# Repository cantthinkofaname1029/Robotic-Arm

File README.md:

Robotic Arm
===========

2015 Robotic Arm Hardware/Software
- Please see the wiki for more information about the subjects below.

Hardware:
---------

###PCBs
-Version 3 of the arm board aka "the old-new arm board" is a remake of V2 (the old arm board currently on Phoenix). It is designed to have the exact same functionality as Phoenix, without using a master-slave protocol. It features a TI Launchpad Stellaris as the central CPU, 3 motor controllers that can connect to up to two motors each, and an RS-485 connection to the old dynamixel (MX-64R). It has the additional capability of communicating with the end effector via XBee and receives power from PORN.

-Version 4 of the arm board aka "the illuminati board" is the latest version. It features a TIVA-C for it's central processor and extends the functionality of Version 3. It only has one motor controller for the Pololu actuator, but it connects to multiple Dynamixels over TTL. There is a 9DOF IMU added on the board for additional control capabilities. it also receives power from PORN.

###Motors
-The base of the arm as well as the elbow joints use the Dynamixel MX-64T. It operates at a MAXIMUM voltage of 14.8V. Information on these motors can be found here:

http://support.robotis.com/en/product/dynamixel/mx_series/mx-64.htm

http://support.robotis.com/en/techsupport_eng.htm#product/dynamixel/mx_series/mx-64.htm

http://support.robotis.com/en/techsupport_eng.htm#software/dynamixelsdk.htm

-The wrist joints on the arm use the Dynamixel MX-28T. It operates at a MAXIMUM voltage of 14.8V. Information on these motors can be found here:

http://support.robotis.com/en/product/dynamixel/mx_series/mx-28.htm

http://support.robotis.com/en/techsupport_eng.htm#product/dynamixel/mx_series/mx-28.htm

http://support.robotis.com/en/techsupport_eng.htm#software/dynamixelsdk.htm

-The shoulder joint of the arm uses a Pololu Linear Actuator with an 8" stroke and a potentiometer for feedback. It operates at a MAXIMUM of 12V. It will be controlled using an on-board motor controller. Information on this actuator can be found here:

https://www.pololu.com/product/2337/specs

Software:
---------

-Software for V3 is nearing completion. It will have basic functionality for the arm for open-loop controls.

-Software for V4 has not started yet. It will be a port from the V3 code to TivaWare.

-After the V4 code has been completed for basic functionality, we need to start writing the framework for more exotic control methods.

-There is a Dynamixel SDK found here:

http://support.robotis.com/en/software/dynamixelsdk.htm

-There is a fully-written Dynamixel Library written for Arduino here:

http://savageelectronics.blogspot.com/2011/01/arduino-y-dynamixel-ax-12.html

if you can't read spanish or use google translate, the various libraries are found here:

http://savageelectronics.blogspot.com/2011/08/actualizacion-biblioteca-dynamixel.html

These will probably be useful to us when writing the further code.

-We may have to write our own PID control for the actuator in the future. Get an introduction to PID for arduino here:

http://brettbeauregard.com/blog/2011/04/improving-the-beginners-pid-introduction/

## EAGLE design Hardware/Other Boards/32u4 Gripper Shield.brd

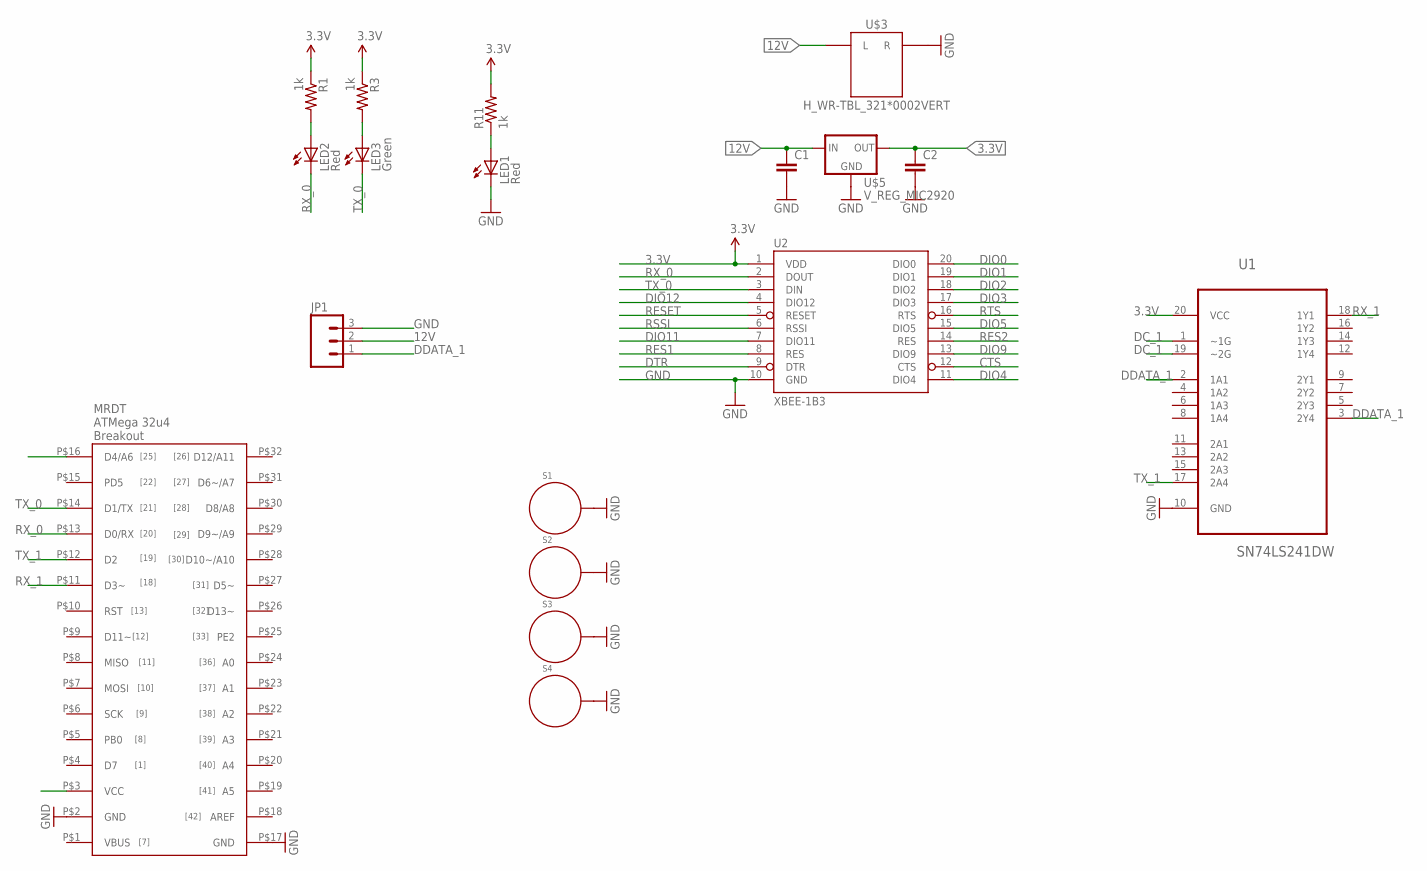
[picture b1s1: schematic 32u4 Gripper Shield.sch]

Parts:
C1, C2: CAP1206; 1206
JP1: M03PTH; 1X03
LED1, LED2: Red; LED-0603
LED3: Green; LED-0603
R1, R3, R11: 1k; 1206
S1, S2, S3, S4: STANDOFF_ELECTRICAL; STANDOFF-ELECTRICAL
U1: SN74LS241DW; SOIC127P1030X265-20N
U2: XBEE-1B3; XBEE-SMD
U$1: 32U4_BREAKOU_SMD; 32U3_MCU_DIP_SMD
U$3: H_WR-TBL_321*0002VERT; 691321100002
U$5: V_REG_MIC2920; SOT223

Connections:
3.3V: C2.1, R1.1, R3.1, R11.2, U1.20 (VCC), U2.1 (VDD), U$1.P$3 (VCC), U$5.3 (OUT)
12V: C1.1, JP1.2, U$3.L, U$5.1 (IN)
CTS: U2.12 (CTS)
DC_1: U1.1 (~1G), U1.19 (~2G), U$1.P$16 (D4/A6)
DDATA_1: JP1.1, U1.2 (1A1), U1.3 (2Y4)
DIO0: U2.20 (DIO0)
DIO1: U2.19 (DIO1)
DIO2: U2.18 (DIO2)
DIO3: U2.17 (DIO3)
DIO4: U2.11 (DIO4)
DIO5: U2.15 (DIO5)
DIO9: U2.13 (DIO9)
DIO11: U2.7 (DIO11)
DIO12: U2.4 (DIO12)
DTR: U2.9 (DTR)
GND: C1.2, C2.2, JP1.3, LED1.C, S1.P1, S2.P1, S3.P1, S4.P1, U1.10 (GND), U2.10 (GND), U$1.P$2 (GND), U$1.P$17 (GND), U$3.R, U$5.2 (GND), U$5.4 (GND)
unnamed: LED2.A, R1.2
unnamed: LED3.A, R3.2
unnamed: LED1.A, R11.1
RES1: U2.8 (RES)
RES2: U2.14 (RES)
RESET: U2.5 (RESET)
RSSI: U2.6 (RSSI)
RTS: U2.16 (RTS)
RX_0: LED2.C, U2.2 (DOUT), U$1.P$13 (D0/RX)
RX_1: U1.18 (1Y1), U$1.P$11 (D3~)
TX_0: LED3.C, U2.3 (DIN), U$1.P$14 (D1/TX)
TX_1: U1.17 (2A4), U$1.P$12 (D2)

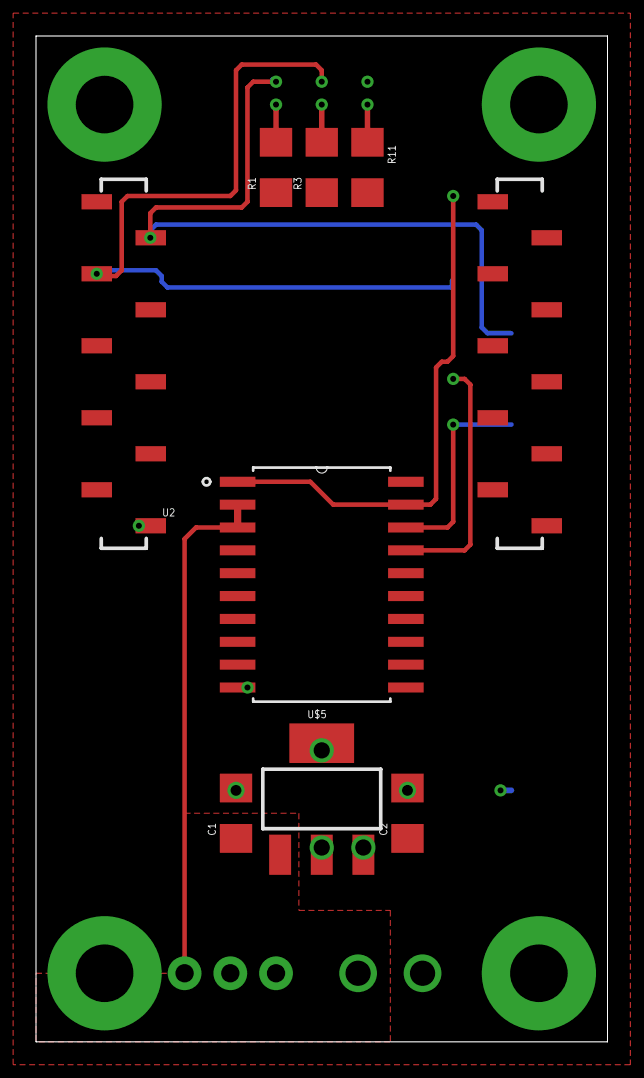
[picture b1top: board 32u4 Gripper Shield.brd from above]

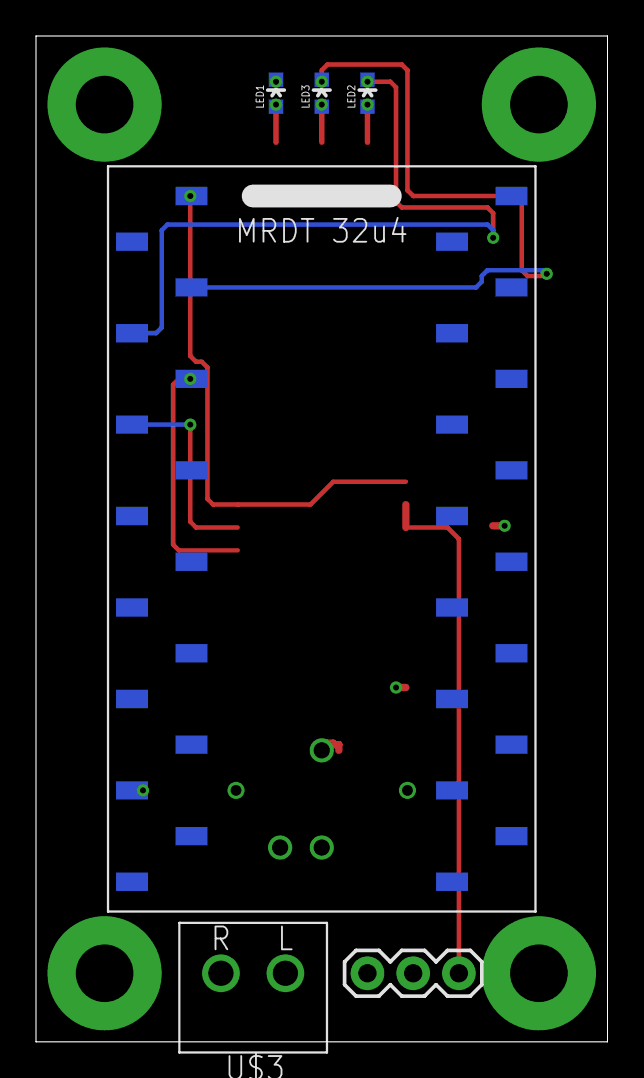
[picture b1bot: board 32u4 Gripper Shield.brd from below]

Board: 2 copper layers, 31.8 x 55.9 mm, 18 parts (6 on the bottom side), 12 nets.

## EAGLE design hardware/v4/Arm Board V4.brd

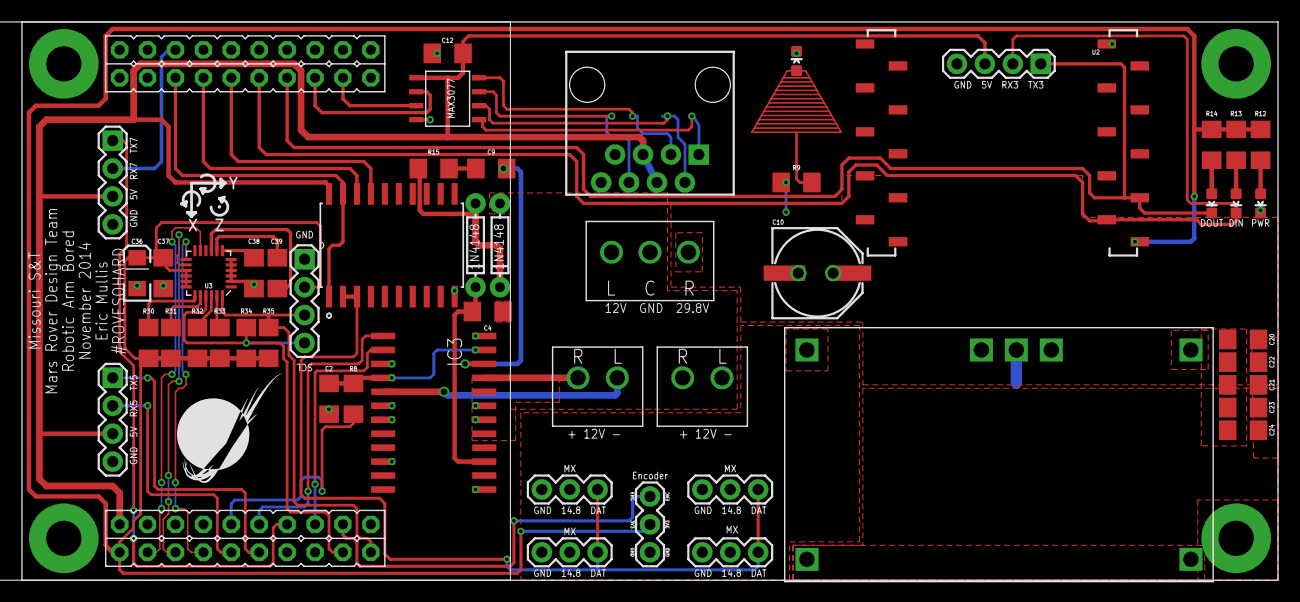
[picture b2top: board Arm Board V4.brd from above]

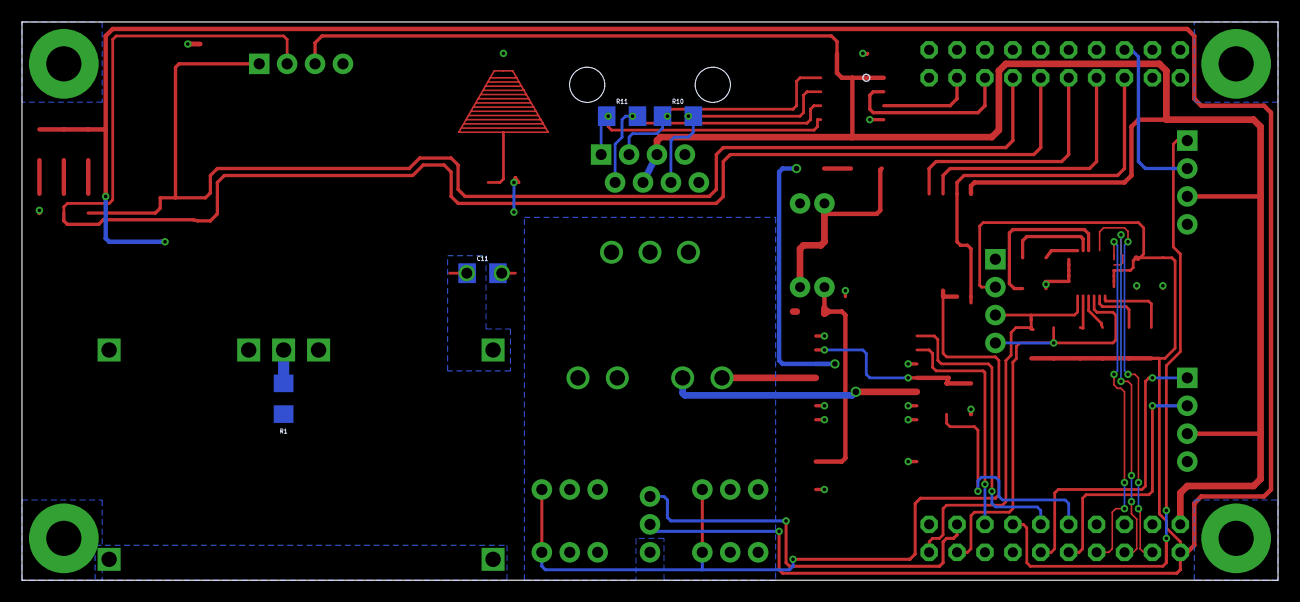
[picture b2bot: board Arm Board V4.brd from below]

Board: 2 copper layers, 114.3 x 50.8 mm, 60 parts (4 on the bottom side), 50 nets.

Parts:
C2: 5.6nF; 1206
C4: 220nF; 1206
C9: 10nF; 1206
C10: 330uF; PANASONIC_E
C11, C20: 1.0uF; 1206
C12: .1uF; 1206
C21, C22, C23, C24, C38: 4.7uF; 1206
C36: 10uF; EIA3216
C37: 1uF; 1206
C39: .22uF; 1206
D1, D2: 1N4148; DIODE-1N4148
IC3: L6206D; SO24
JP1, JP2, JP3, JP4: 1X04
JP7, JP9, JP10, JP11, JP12: 1X03
LED1, LED2, LED5: RED; LED-0603
LED3: GREEN; LED-0603
P1: STELLARIS-LAUNCHPADSTELLARIS-LAUNCHPAD-XL; LAUNCHPAD-XL
R1: 17.2k; 1206
R8: 100k; 1206
R9: 1.5k; 1206
R10, R11: 120 Ohm; 1206
R12, R13, R14: 1k; 1206
R15: 100; 1206
R30, R31, R32, R33, R34, R35: 10k; 1206
S1, S2, S3, S4: STANDOFF_ELECTRICAL; STANDOFF-ELECTRICAL
U1: SN74LS241DW; SOIC127P1030X265-20N
U2: XBEE-1B3; XBEE-SMD
U3: LSM9DS0; LGA-24
U$2: Q_PTN78020; R_PDSS-T7
U$3: RJ45-8PTH; RJ45-8
U$4: MAX3077; MAX3070E
U$5: 691321100003; 691322110003
U$6, U$7: H_WR-TBL_321*0002VERT; 691321100002

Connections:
14.8V: C10.+, C11.1, JP9.2, JP10.2, JP11.2, JP12.2, U$2.6
+3V3: C36.A, C37.1, JP4.2, JP7.2, P1.3.3V, R12.2, R13.1, R14.1, R30.2, R31.2, R32.2, R33.2, R34.2, R35.2, U2.1, U3.15, U3.16, U3.17, U3.18
+5V: C12.1, JP1.3, JP2.3, JP3.3, P1.VBUS, U1.20, U$3.4, U$3.5, U$4.VCC
+12V: C4.1, D2.A, IC3.17, IC3.20, U$5.L, U$7.L
A1: IC3.5, U$6.L
A2: IC3.21, U$6.R
CS_G: R30.1, U3.19
CS_XM: R31.1, U3.20
DC_1: P1.PB3, U1.1, U1.19
DDATA_1: JP9.3, JP10.3, JP11.3, JP12.3, U1.2, U1.3
EN_A: P1.PD2, R8.2
GND: C2.1, C10.-, C11.2, C12.2, C20.2, C21.2, C22.2, C23.2, C24.2, C36.C, C37.2, C38.2, IC3.3, IC3.6, IC3.7, IC3.10, IC3.13, IC3.18, IC3.19, IC3.24, JP1.4, JP2.4, JP3.4, JP4.1, JP7.1, JP9.1, JP10.1, JP11.1, JP12.1, LED1.C, LED5.C, P1.GND1, P1.GND2, R1.1, S1.P1, S2.P1, S3.P1, S4.P1, U1.10, U2.10, U3.2, U3.3, U3.4, U3.5, U3.6, U$2.1, U$2.7, U$3.7, U$3.8, U$4.GND, U$5.C, U$7.R
IN1_A: IC3.1, P1.PD3
IN2_A: IC3.2, P1.PE2
INT1_XM: P1.PB1, U3.13
INT2_XM: P1.PB0, U3.14
INT_G: P1.PB5, U3.11
LA_ENC: JP7.3, P1.PE3
unnamed: R11.1, U$3.2, U$4.Z
unnamed: R10.2, U$3.6, U$4.B
unnamed: R10.1, U$3.3, U$4.A
unnamed: LED2.A, R13.2
unnamed: R11.2, U$3.1, U$4.Y
unnamed: LED3.A, R14.2
unnamed: R1.2, U$2.4
unnamed: C39.1, U3.9
unnamed: C39.2, U3.8
unnamed: C38.1, U3.7
unnamed: LED5.A, R9.1
unnamed: D1.A, D2.C, R15.2
unnamed: C9.2, R15.1
unnamed: C9.1, IC3.22
unnamed: LED1.A, R12.1
OCD_A: C2.2, IC3.4, IC3.23, R8.1
RX_1: P1.PC4, U1.18
RX_2: P1.PD6, U$4.RO
RX_3: JP1.2, LED2.C, P1.PC6, U2.2
RX_5: JP3.2, P1.PE4
RX_7: JP2.2, P1.PE0
SCL: JP4.4, P1.PA6, R34.1, U3.21
SDA: JP4.3, P1.PA7, R35.1, U3.24
SDO_G: R32.1, U3.22
SDO_XM: R33.1, U3.23
TX_1: P1.PC5, U1.17
TX_2: P1.PD7, U$4.DI
TX_3: JP1.1, LED3.C, P1.PC7, U2.3
TX_5: JP3.1, P1.PE5
TX_7: JP2.1, P1.PE1
VBOOT: C4.2, D1.C, IC3.15
VIN: C20.1, C21.1, C22.1, C23.1, C24.1, R9.2, U$2.2, U$5.R

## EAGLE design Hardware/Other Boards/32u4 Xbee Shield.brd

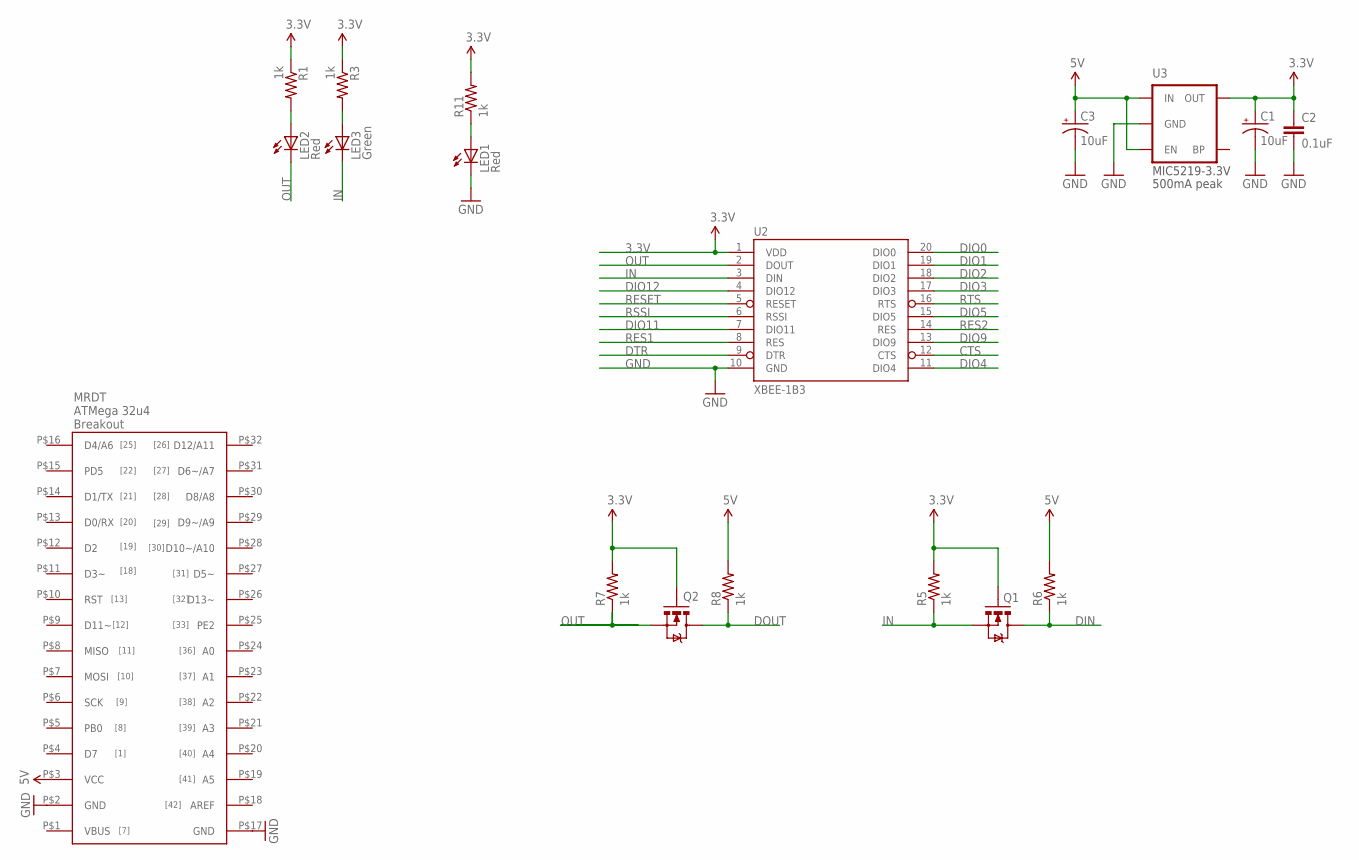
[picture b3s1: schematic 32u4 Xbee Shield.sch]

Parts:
C1, C3: 10uF; EIA3216
C2: 0.1uF; 1206
LED1, LED2: Red; LED-0603
LED3: Green; LED-0603
Q1, Q2: MOSFET-NCHANNELSMD; SOT23-3
R1, R3, R5, R6, R7, R8, R11: 1k; 1206
U2: XBEE-1B3; XBEE-SMD
U3: V_REG_LDOSMD; SOT23-5
U$1: 32U4_BREAKOU_SMD; 32U3_MCU_DIP_SMD

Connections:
3.3V: C1.A (+), C2.1, Q1.1 (G), Q2.1 (G), R1.1, R3.1, R5.2, R7.2, R11.2, U2.1 (VDD), U3.5 (OUT)
5V: C3.A (+), R6.2, R8.2, U3.1 (IN), U3.3 (EN), U$1.P$3 (VCC)
CTS: U2.12 (CTS)
DIN: Q1.3 (D), R6.1
DIO0: U2.20 (DIO0)
DIO1: U2.19 (DIO1)
DIO2: U2.18 (DIO2)
DIO3: U2.17 (DIO3)
DIO4: U2.11 (DIO4)
DIO5: U2.15 (DIO5)
DIO9: U2.13 (DIO9)
DIO11: U2.7 (DIO11)
DIO12: U2.4 (DIO12)
DOUT: Q2.3 (D), R8.1
DTR: U2.9 (DTR)
GND: C1.C (-), C2.2, C3.C (-), LED1.C, U2.10 (GND), U3.2 (GND), U$1.P$2 (GND), U$1.P$17 (GND)
IN: LED3.C, Q1.2 (S), R5.1, U2.3 (DIN)
unnamed: LED2.A, R1.2
unnamed: LED3.A, R3.2
unnamed: LED1.A, R11.1
OUT: LED2.C, Q2.2 (S), R7.1, U2.2 (DOUT)
RES1: U2.8 (RES)
RES2: U2.14 (RES)
RESET: U2.5 (RESET)
RSSI: U2.6 (RSSI)
RTS: U2.16 (RTS)

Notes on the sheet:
MIC5219-3.3V
500mA peak

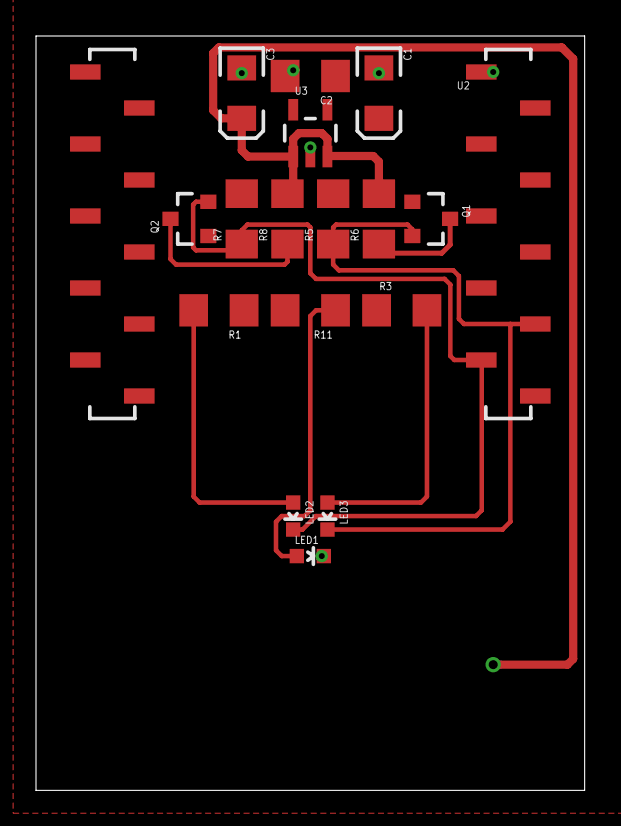
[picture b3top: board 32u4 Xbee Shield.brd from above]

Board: 2 copper layers, 30.5 x 41.9 mm, 18 parts (1 on the bottom side), 10 nets.

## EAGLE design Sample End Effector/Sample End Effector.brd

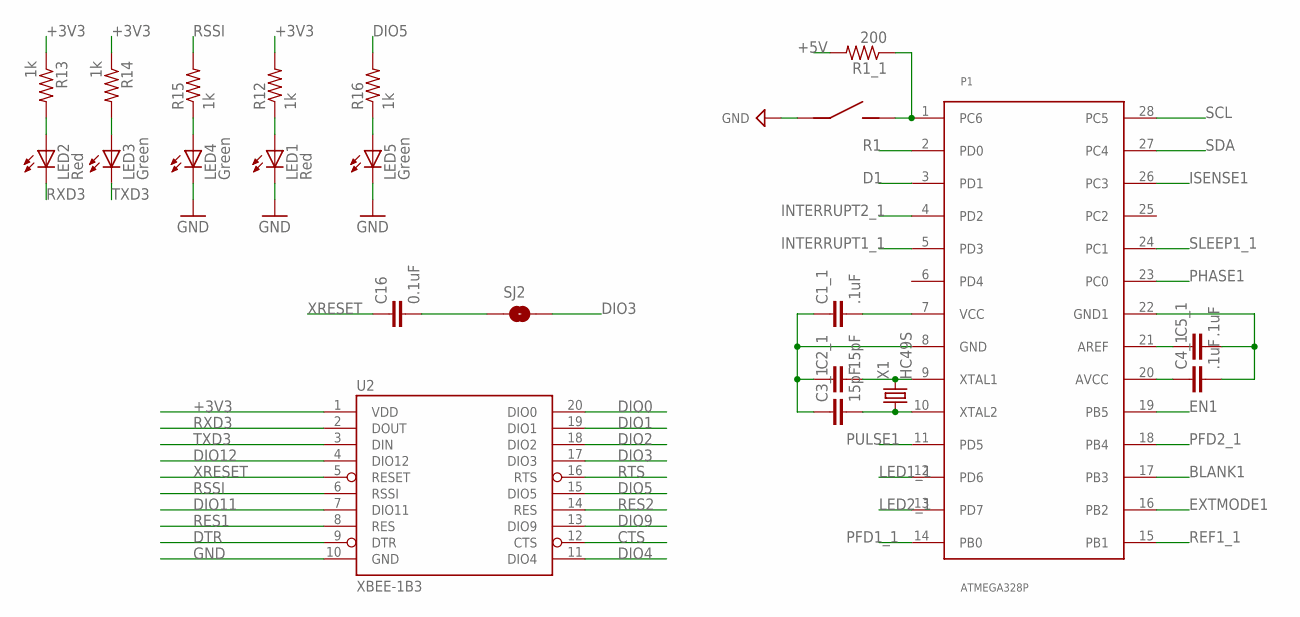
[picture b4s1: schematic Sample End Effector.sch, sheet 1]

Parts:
C1_1, C4_1, C5_1: .1uF; C_0805
C2_1, C3_1: 15pF; C_0805
C16: 0.1uF; 0603-CAP
LED1, LED2: Red; LED-0603
LED3, LED4, LED5: Green; LED-0603
P1: ATMEGA328P; DIP28
R1_1: 200; R_0805
R12, R13, R14, R15, R16: 1k; 0603-RES
S1: J_MC32857; J_TOGGLE
SJ2: SOLDERJUMPERTRACE; SJ_2S-TRACE
U2: XBEE-1B3; XBEE-SMD
X1: HC49S; HC-49

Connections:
+3V3: R12.2, R13.1, R14.1, U2.1 (VDD); also elsewhere on the board
+5V: C1_1.2, C4_1.1, P1.7 (VCC), P1.20 (AVCC), R1_1.2; also elsewhere on the board
BLANK1: P1.17 (PB3)
CTS: U2.12 (CTS)
D1: P1.3 (PD1)
DIO0: U2.20 (DIO0)
DIO1: U2.19 (DIO1)
DIO2: U2.18 (DIO2)
DIO3: SJ2.2, U2.17 (DIO3)
DIO4: U2.11 (DIO4)
DIO5: R16.2, U2.15 (DIO5)
DIO9: U2.13 (DIO9)
DIO11: U2.7 (DIO11)
DIO12: U2.4 (DIO12)
DTR: U2.9 (DTR)
EN1: P1.19 (PB5)
EXTMODE1: P1.16 (PB2)
GND: C1_1.1, C2_1.1, C3_1.1, C4_1.2, C5_1.2, LED1.C, LED4.C, LED5.C, P1.8 (GND), P1.22 (GND1), S1.P$1 (1), U2.10 (GND); also elsewhere on the board
INTERRUPT1_1: P1.5 (PD3)
INTERRUPT2_1: P1.4 (PD2)
ISENSE1: P1.26 (PC3)
LED1_1: P1.12 (PD6)
LED2_1: P1.13 (PD7)
unnamed: C3_1.2, P1.10 (XTAL2), X1.P$1 (1)
unnamed: LED2.A, R13.2
unnamed: LED3.A, R14.2
unnamed: LED4.A, R15.1
unnamed: C16.2, SJ2.1
unnamed: C2_1.2, P1.9 (XTAL1), X1.P$2 (2)
unnamed: C5_1.1, P1.21 (AREF)
unnamed: P1.1 (PC6), R1_1.1, S1.P$2 (2)
unnamed: LED1.A, R12.1
unnamed: LED5.A, R16.1
PFD1_1: P1.14 (PB0)
PFD2_1: P1.18 (PB4)
PHASE1: P1.23 (PC0)
PULSE1: P1.11 (PD5)
R1: P1.2 (PD0)
REF1_1: P1.15 (PB1)
RES1: U2.8 (RES)
RES2: U2.14 (RES)
RSSI: R15.2, U2.6 (RSSI)
RTS: U2.16 (RTS)
RXD3: LED2.C, U2.2 (DOUT)
SCL: P1.28 (PC5)
SDA: P1.27 (PC4)
SLEEP1_1: P1.24 (PC1)
TXD3: LED3.C, U2.3 (DIN)
XRESET: C16.1, U2.5 (RESET)

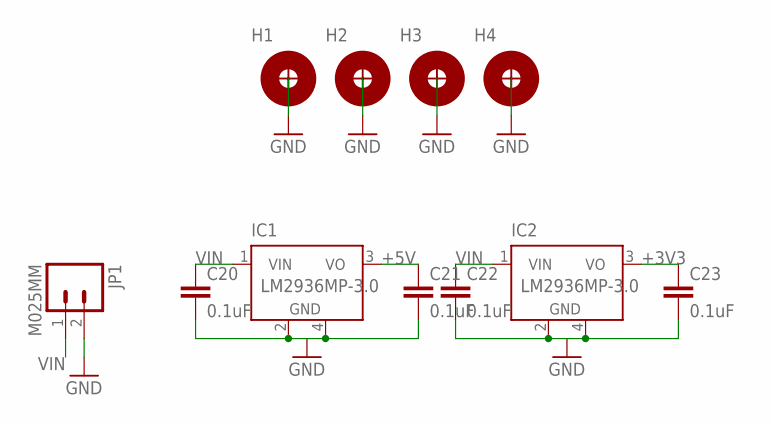
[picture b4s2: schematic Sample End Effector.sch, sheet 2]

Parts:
C20, C21, C22, C23: 0.1uF; 0603-CAP
H1, H2, H3, H4: H_MNTHOLE_#4
IC1, IC2: LM2936MP-3.0; SOT223
JP1: M025MM; SCREWTERMINAL-5MM-2

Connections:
+3V3: C23.1, IC2.3 (VO); also elsewhere on the board
+5V: C21.1, IC1.3 (VO); also elsewhere on the board
GND: C20.2, C21.2, C22.2, C23.2, H1.1, H2.1, H3.1, H4.1, IC1.2 (GND), IC1.4 (GND), IC2.2 (GND), IC2.4 (GND), JP1.2; also elsewhere on the board
VIN: C20.1, C22.1, IC1.1 (VIN), IC2.1 (VIN), JP1.1

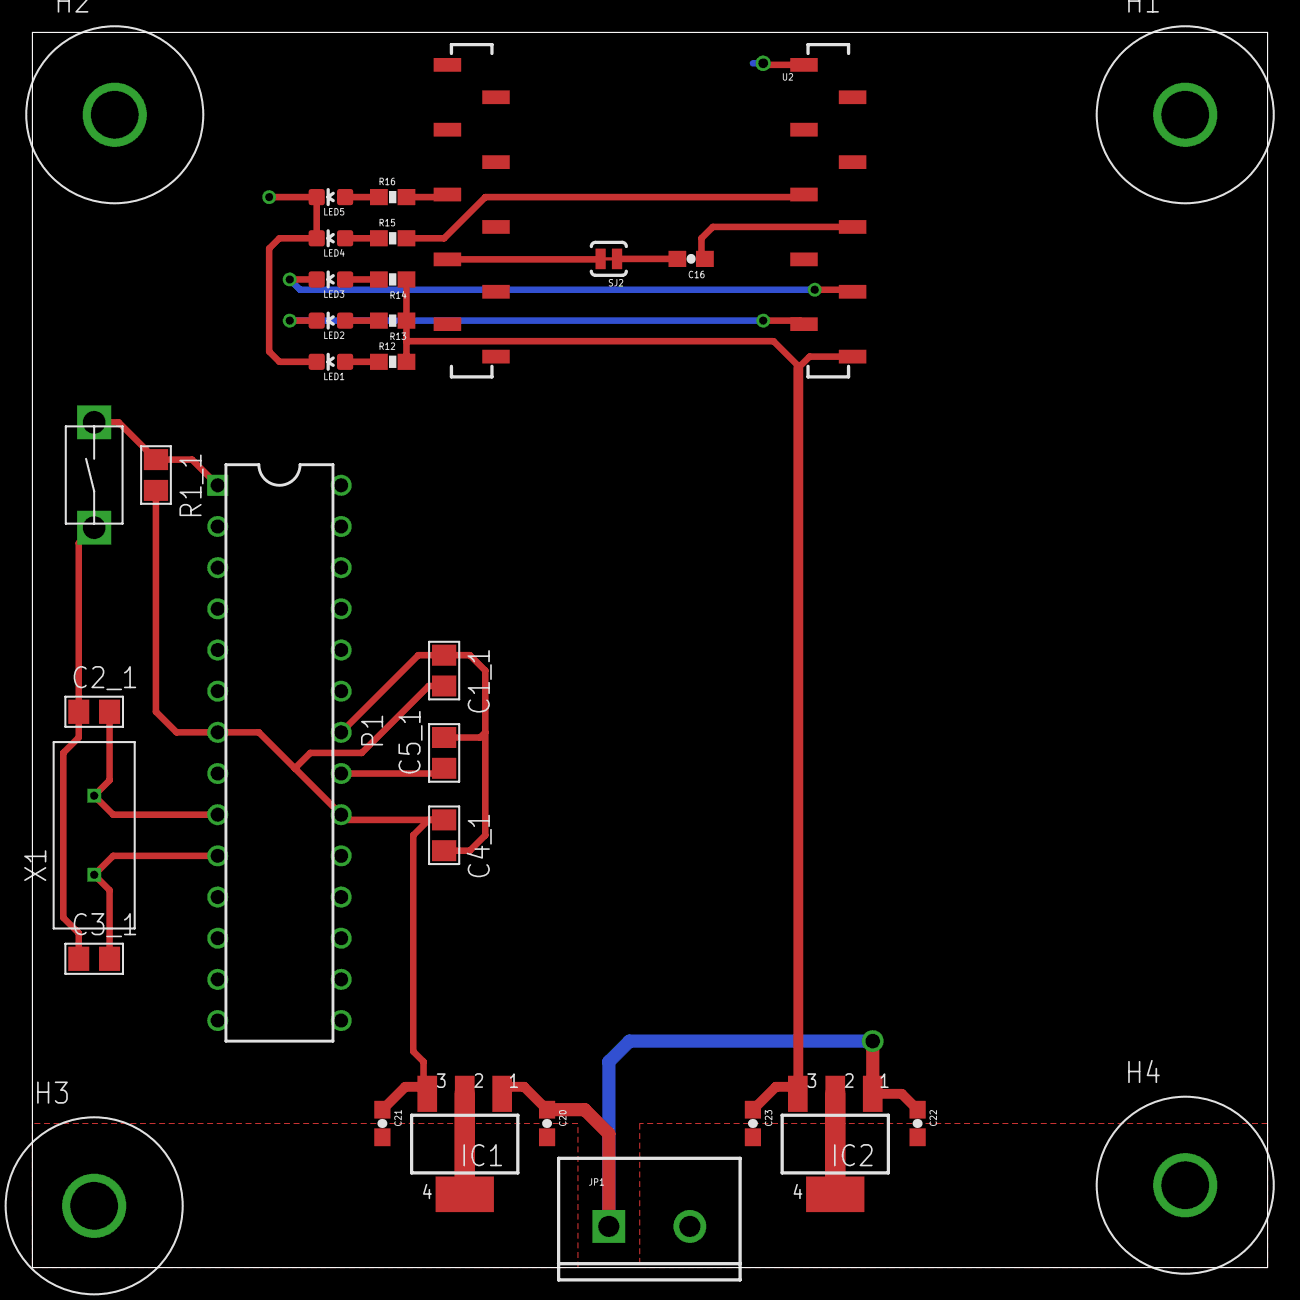
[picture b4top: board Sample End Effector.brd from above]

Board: 2 copper layers, 76.2 x 76.2 mm, 33 parts (0 on the bottom side), 20 nets.

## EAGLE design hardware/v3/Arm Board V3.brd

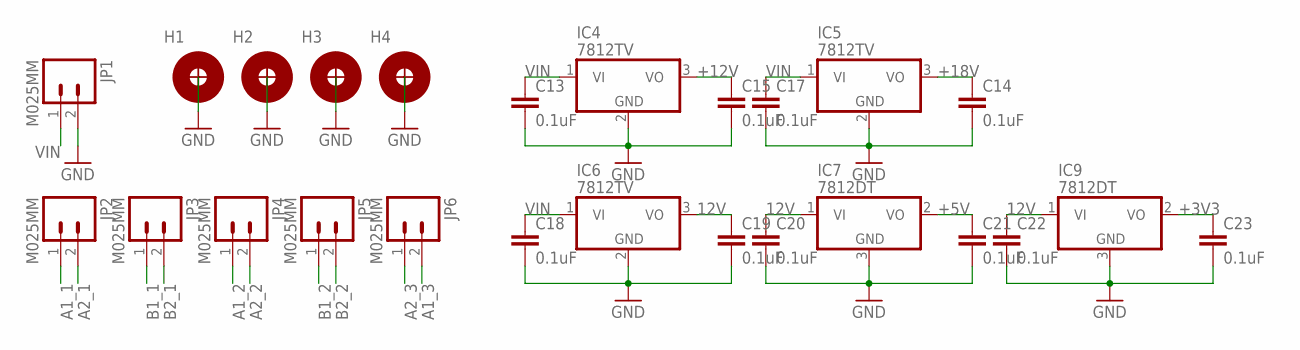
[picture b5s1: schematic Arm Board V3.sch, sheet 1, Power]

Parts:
C13, C14, C15, C17, C18, C19, C20, C21, C22, C23: 0.1uF; 0603-CAP
H1, H2, H3, H4: H_MNTHOLE_#4
IC4, IC5, IC6: 7812TV; TO220V
IC7, IC9: 7812DT; TO252
JP1, JP2, JP3, JP4, JP5, JP6: M025MM; SCREWTERMINAL-5MM-2

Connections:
12V: C19.1, C20.1, C22.1, IC6.3 (VO), IC7.1 (VI), IC9.1 (VI)
+3V3: C23.1, IC9.2 (VO); also elsewhere on the board
+5V: C21.1, IC7.2 (VO); also elsewhere on the board
+12V: C15.1, IC4.3 (VO); also elsewhere on the board
+18V: C14.1, IC5.3 (VO); also elsewhere on the board
A1_1: JP2.1; also elsewhere on the board
A1_2: JP4.1; also elsewhere on the board
A1_3: JP6.2; also elsewhere on the board
A2_1: JP2.2; also elsewhere on the board
A2_2: JP4.2; also elsewhere on the board
A2_3: JP6.1; also elsewhere on the board
B1_1: JP3.1; also elsewhere on the board
B1_2: JP5.1; also elsewhere on the board
B2_1: JP3.2; also elsewhere on the board
B2_2: JP5.2; also elsewhere on the board
GND: C13.2, C14.2, C15.2, C17.2, C18.2, C19.2, C20.2, C21.2, C22.2, C23.2, H1.1, H2.1, H3.1, H4.1, IC4.2 (GND), IC5.2 (GND), IC6.2 (GND), IC7.3 (GND), IC9.3 (GND), JP1.2; also elsewhere on the board
VIN: C13.1, C17.1, C18.1, IC4.1 (VI), IC5.1 (VI), IC6.1 (VI), JP1.1; also elsewhere on the board

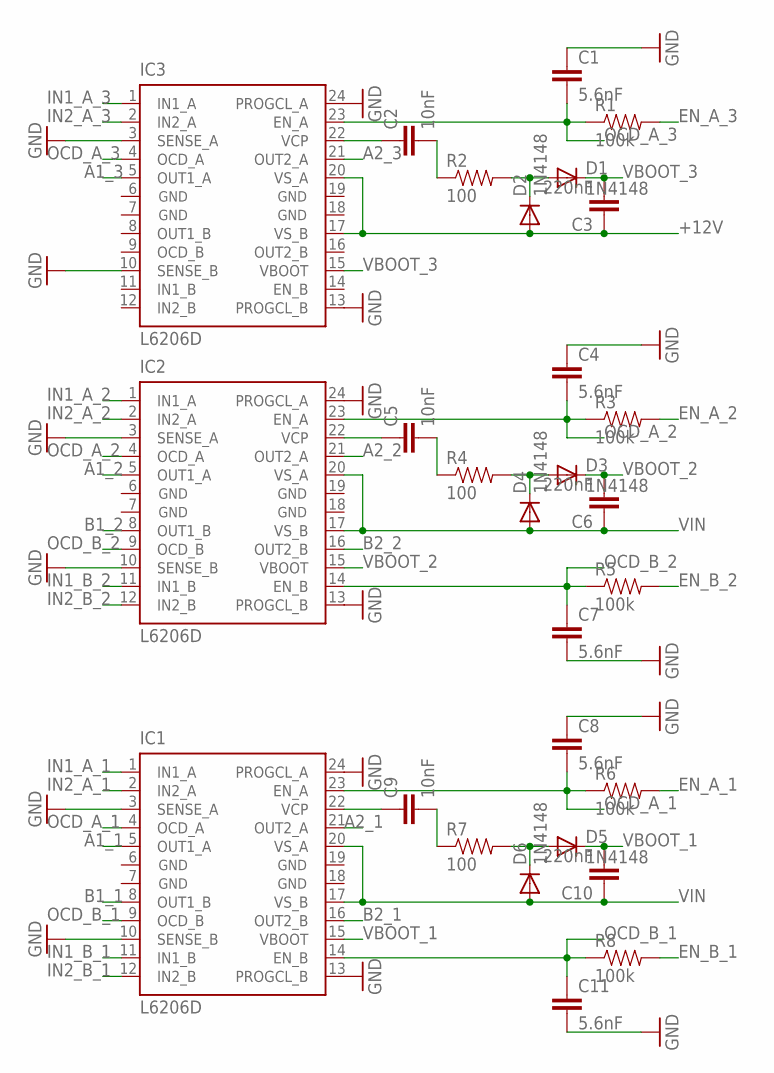
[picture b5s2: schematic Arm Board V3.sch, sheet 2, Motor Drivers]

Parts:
C1, C4, C7, C8, C11: 5.6nF; 0603-CAP
C2, C5, C9: 10nF; 0603-CAP
C3, C6, C10: 220nF; 0603-CAP
D1, D2, D3, D4, D5, D6: 1N4148; DIODE-1N4148
IC1, IC2, IC3: L6206D; SO24
R1, R3, R5, R6, R8: 100k; 0805
R2, R4, R7: 100; 0805

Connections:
+12V: C3.1, D2.A, IC3.17 (VS_B), IC3.20 (VS_A); also elsewhere on the board
A1_1: IC1.5 (OUT1_A); also elsewhere on the board
A1_2: IC2.5 (OUT1_A); also elsewhere on the board
A1_3: IC3.5 (OUT1_A); also elsewhere on the board
A2_1: IC1.21 (OUT2_A); also elsewhere on the board
A2_2: IC2.21 (OUT2_A); also elsewhere on the board
A2_3: IC3.21 (OUT2_A); also elsewhere on the board
B1_1: IC1.8 (OUT1_B); also elsewhere on the board
B1_2: IC2.8 (OUT1_B); also elsewhere on the board
B2_1: IC1.16 (OUT2_B); also elsewhere on the board
B2_2: IC2.16 (OUT2_B); also elsewhere on the board
EN_A_1: R6.2; also elsewhere on the board
EN_A_2: R3.2; also elsewhere on the board
EN_A_3: R1.2; also elsewhere on the board
EN_B_1: R8.2; also elsewhere on the board
EN_B_2: R5.2; also elsewhere on the board
GND: C1.1, C4.1, C7.2, C8.1, C11.2, IC1.3 (SENSE_A), IC1.6 (GND), IC1.7 (GND), IC1.10 (SENSE_B), IC1.13 (PROGCL_B), IC1.18 (GND), IC1.19 (GND), IC1.24 (PROGCL_A), IC2.3 (SENSE_A), IC2.6 (GND), IC2.7 (GND), IC2.10 (SENSE_B), IC2.13 (PROGCL_B), IC2.18 (GND), IC2.19 (GND), IC2.24 (PROGCL_A), IC3.3 (SENSE_A), IC3.6 (GND), IC3.7 (GND), IC3.10 (SENSE_B), IC3.13 (PROGCL_B), IC3.18 (GND), IC3.19 (GND), IC3.24 (PROGCL_A); also elsewhere on the board
IN1_A_1: IC1.1 (IN1_A); also elsewhere on the board
IN1_A_2: IC2.1 (IN1_A); also elsewhere on the board
IN1_A_3: IC3.1 (IN1_A); also elsewhere on the board
IN1_B_1: IC1.11 (IN1_B); also elsewhere on the board
IN1_B_2: IC2.11 (IN1_B); also elsewhere on the board
IN2_A_1: IC1.2 (IN2_A); also elsewhere on the board
IN2_A_2: IC2.2 (IN2_A); also elsewhere on the board
IN2_A_3: IC3.2 (IN2_A); also elsewhere on the board
IN2_B_1: IC1.12 (IN2_B); also elsewhere on the board
IN2_B_2: IC2.12 (IN2_B); also elsewhere on the board
unnamed: D3.A, D4.C, R4.2
unnamed: D5.A, D6.C, R7.2
unnamed: C5.2, R4.1
unnamed: C9.1, IC1.22 (VCP)
unnamed: C9.2, R7.1
unnamed: C5.1, IC2.22 (VCP)
unnamed: D1.A, D2.C, R2.2
unnamed: C2.2, R2.1
unnamed: C2.1, IC3.22 (VCP)
OCD_A_1: C8.2, IC1.4 (OCD_A), IC1.23 (EN_A), R6.1
OCD_A_2: C4.2, IC2.4 (OCD_A), IC2.23 (EN_A), R3.1
OCD_A_3: C1.2, IC3.4 (OCD_A), IC3.23 (EN_A), R1.1
OCD_B_1: C11.1, IC1.9 (OCD_B), IC1.14 (EN_B), R8.1
OCD_B_2: C7.1, IC2.9 (OCD_B), IC2.14 (EN_B), R5.1
VBOOT_1: C10.2, D5.C, IC1.15 (VBOOT)
VBOOT_2: C6.2, D3.C, IC2.15 (VBOOT)
VBOOT_3: C3.2, D1.C, IC3.15 (VBOOT)
VIN: C6.1, C10.1, D4.A, D6.A, IC1.17 (VS_B), IC1.20 (VS_A), IC2.17 (VS_B), IC2.20 (VS_A); also elsewhere on the board

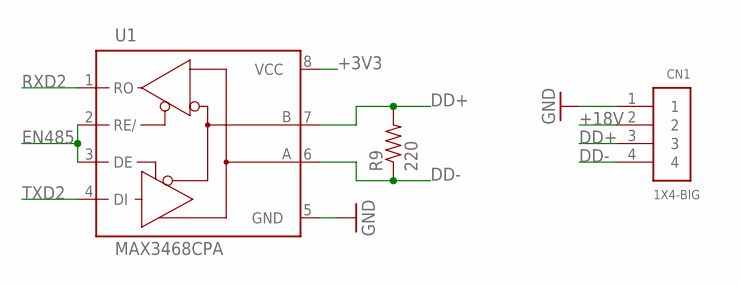
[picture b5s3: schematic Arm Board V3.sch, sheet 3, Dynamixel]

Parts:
CN1: 1X4-BIG; 1X04-BIG
R9: 220; 0603-RES
U1: MAX3468CPA; DIL08

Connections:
+3V3: U1.8 (VCC); also elsewhere on the board
+18V: CN1.2; also elsewhere on the board
DD+: CN1.3, R9.2, U1.7 (B)
DD-: CN1.4, R9.1, U1.6 (A)
EN485: U1.2 (RE/), U1.3 (DE); also elsewhere on the board
GND: CN1.1, U1.5 (GND); also elsewhere on the board
RXD2: U1.1 (RO); also elsewhere on the board
TXD2: U1.4 (DI); also elsewhere on the board

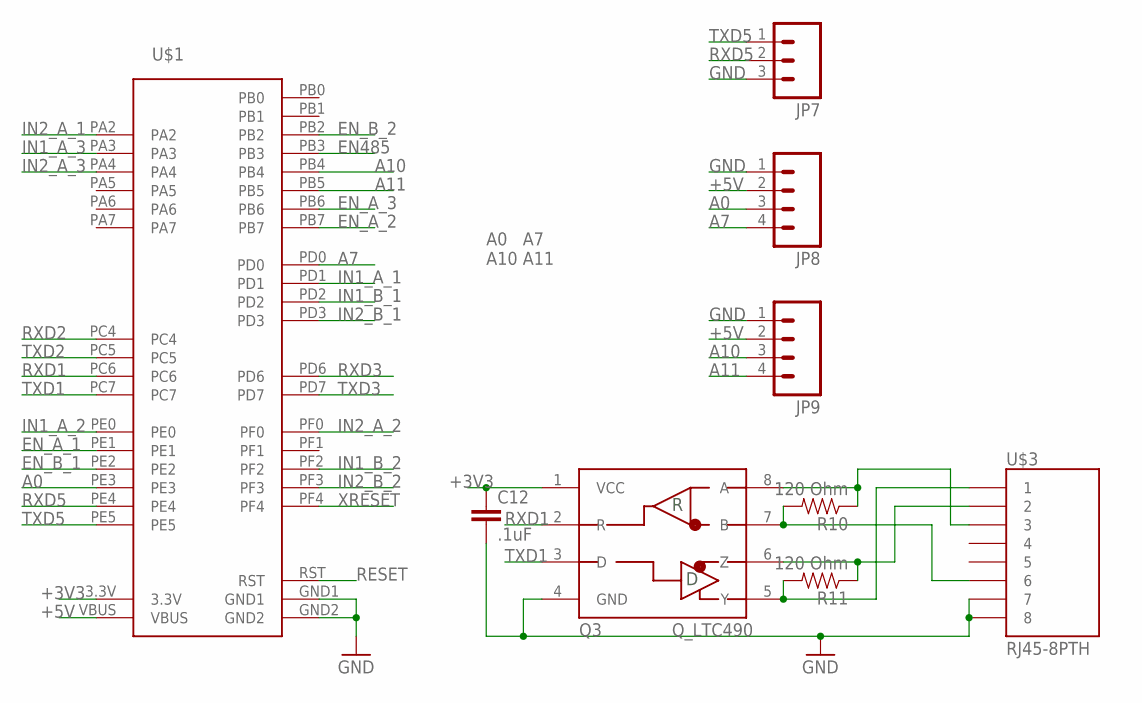
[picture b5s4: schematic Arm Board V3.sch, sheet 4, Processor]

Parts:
C12: .1uF; 0603-CAP
JP7: M03PTH; 1X03
JP8, JP9: M04PTH; 1X04
Q3: Q_LTC490; DIP8
R10, R11: 120 Ohm; 0603-RES
U$1: STELLARIS-LAUNCHPADSTELLARIS-LAUNCHPAD-XL; LAUNCHPAD-XL
U$3: RJ45-8PTH; RJ45-8

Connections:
+3V3: C12.1, Q3.1 (VCC), U$1.3.3V; also elsewhere on the board
+5V: JP8.2, JP9.2, U$1.VBUS; also elsewhere on the board
A0: JP8.3, U$1.PE3
A7: JP8.4, U$1.PD0
A10: JP9.3, U$1.PB4
A11: JP9.4, U$1.PB5
EN485: U$1.PB3; also elsewhere on the board
EN_A_1: U$1.PE1; also elsewhere on the board
EN_A_2: U$1.PB7; also elsewhere on the board
EN_A_3: U$1.PB6; also elsewhere on the board
EN_B_1: U$1.PE2; also elsewhere on the board
EN_B_2: U$1.PB2; also elsewhere on the board
GND: C12.2, JP7.3, JP8.1, JP9.1, Q3.4 (GND), U$1.GND1, U$1.GND2, U$3.7, U$3.8; also elsewhere on the board
IN1_A_1: U$1.PD1; also elsewhere on the board
IN1_A_2: U$1.PE0; also elsewhere on the board
IN1_A_3: U$1.PA3; also elsewhere on the board
IN1_B_1: U$1.PD2; also elsewhere on the board
IN1_B_2: U$1.PF2; also elsewhere on the board
IN2_A_1: U$1.PA2; also elsewhere on the board
IN2_A_2: U$1.PF0; also elsewhere on the board
IN2_A_3: U$1.PA4; also elsewhere on the board
IN2_B_1: U$1.PD3; also elsewhere on the board
IN2_B_2: U$1.PF3; also elsewhere on the board
unnamed: Q3.6 (Z), R11.1, U$3.2
unnamed: Q3.7 (B), R10.2, U$3.6
unnamed: Q3.8 (A), R10.1, U$3.3
unnamed: Q3.5 (Y), R11.2, U$3.1
RESET: U$1.RST
RXD1: Q3.2 (R), U$1.PC6
RXD2: U$1.PC4; also elsewhere on the board
RXD3: U$1.PD6; also elsewhere on the board
RXD5: JP7.2, U$1.PE4
TXD1: Q3.3 (D), U$1.PC7
TXD2: U$1.PC5; also elsewhere on the board
TXD3: U$1.PD7; also elsewhere on the board
TXD5: JP7.1, U$1.PE5
XRESET: U$1.PF4; also elsewhere on the board

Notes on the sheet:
A0 A7 A10 A11

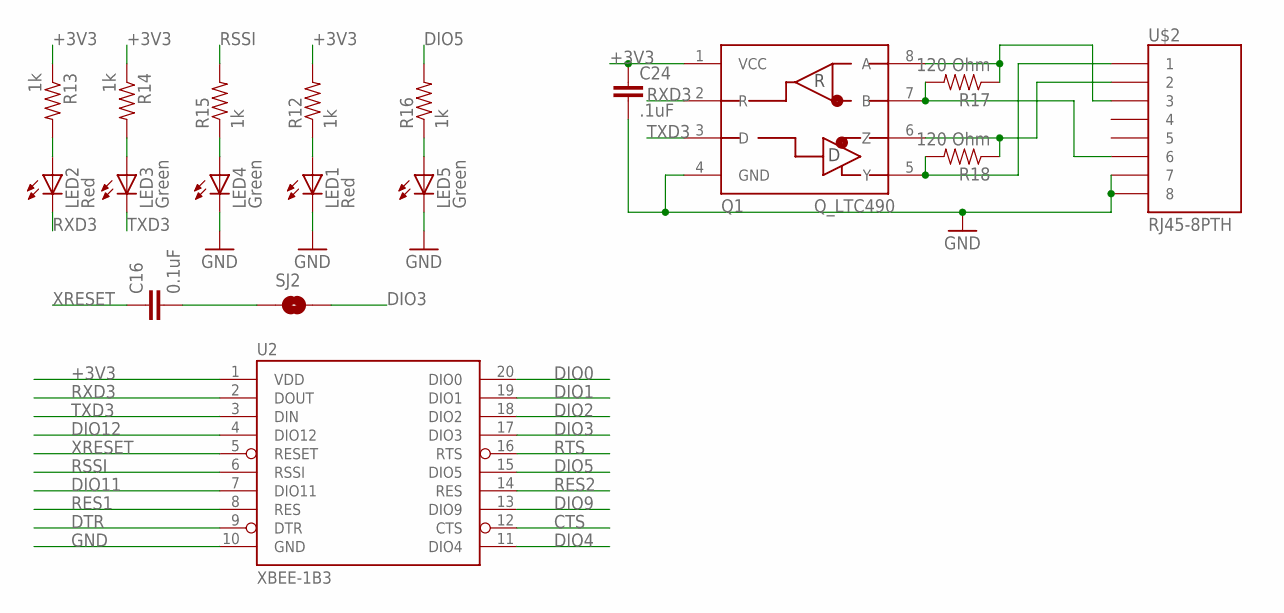
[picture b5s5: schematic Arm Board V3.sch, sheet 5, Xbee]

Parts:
C16: 0.1uF; 0603-CAP
C24: .1uF; 0603-CAP
LED1, LED2: Red; LED-0603
LED3, LED4, LED5: Green; LED-0603
Q1: Q_LTC490; DIP8
R12, R13, R14, R15, R16: 1k; 0603-RES
R17, R18: 120 Ohm; 0603-RES
SJ2: SOLDERJUMPERTRACE; SJ_2S-TRACE
U2: XBEE-1B3; XBEE-SMD
U$2: RJ45-8PTH; RJ45-8

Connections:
+3V3: C24.1, Q1.1 (VCC), R12.2, R13.1, R14.1, U2.1 (VDD); also elsewhere on the board
CTS: U2.12 (CTS)
DIO0: U2.20 (DIO0)
DIO1: U2.19 (DIO1)
DIO2: U2.18 (DIO2)
DIO3: SJ2.2, U2.17 (DIO3)
DIO4: U2.11 (DIO4)
DIO5: R16.2, U2.15 (DIO5)
DIO9: U2.13 (DIO9)
DIO11: U2.7 (DIO11)
DIO12: U2.4 (DIO12)
DTR: U2.9 (DTR)
GND: C24.2, LED1.C, LED4.C, LED5.C, Q1.4 (GND), U2.10 (GND), U$2.7, U$2.8; also elsewhere on the board
unnamed: LED2.A, R13.2
unnamed: LED3.A, R14.2
unnamed: LED4.A, R15.1
unnamed: C16.2, SJ2.1
unnamed: Q1.5 (Y), R18.2, U$2.1
unnamed: Q1.6 (Z), R18.1, U$2.2
unnamed: Q1.7 (B), R17.2, U$2.6
unnamed: Q1.8 (A), R17.1, U$2.3
unnamed: LED1.A, R12.1
unnamed: LED5.A, R16.1
RES1: U2.8 (RES)
RES2: U2.14 (RES)
RSSI: R15.2, U2.6 (RSSI)
RTS: U2.16 (RTS)
RXD3: LED2.C, Q1.2 (R), U2.2 (DOUT); also elsewhere on the board
TXD3: LED3.C, Q1.3 (D), U2.3 (DIN); also elsewhere on the board
XRESET: C16.1, U2.5 (RESET); also elsewhere on the board

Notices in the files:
parts and their libraries:
SparkFun-Connectors: Licensing: Creative Commons ShareAlike 4.0 International - https://creativecommons.org/licenses/by-sa/4.0
SparkFun-DiscreteSemi: Licensing: CC v3.0 Share-Alike You are welcome to use this library for commercial purposes.
